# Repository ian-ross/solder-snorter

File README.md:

# Solder Snorter: a PC fan solder fume extractor

*Solder Snorter* is a project I used to learn a little about battery
charging and power conversion. You can read about it
[here](https://www.skybluetrades.net/projects/solder-snorter).

Designed with [KiCad](https://kicad-pcb.org/).

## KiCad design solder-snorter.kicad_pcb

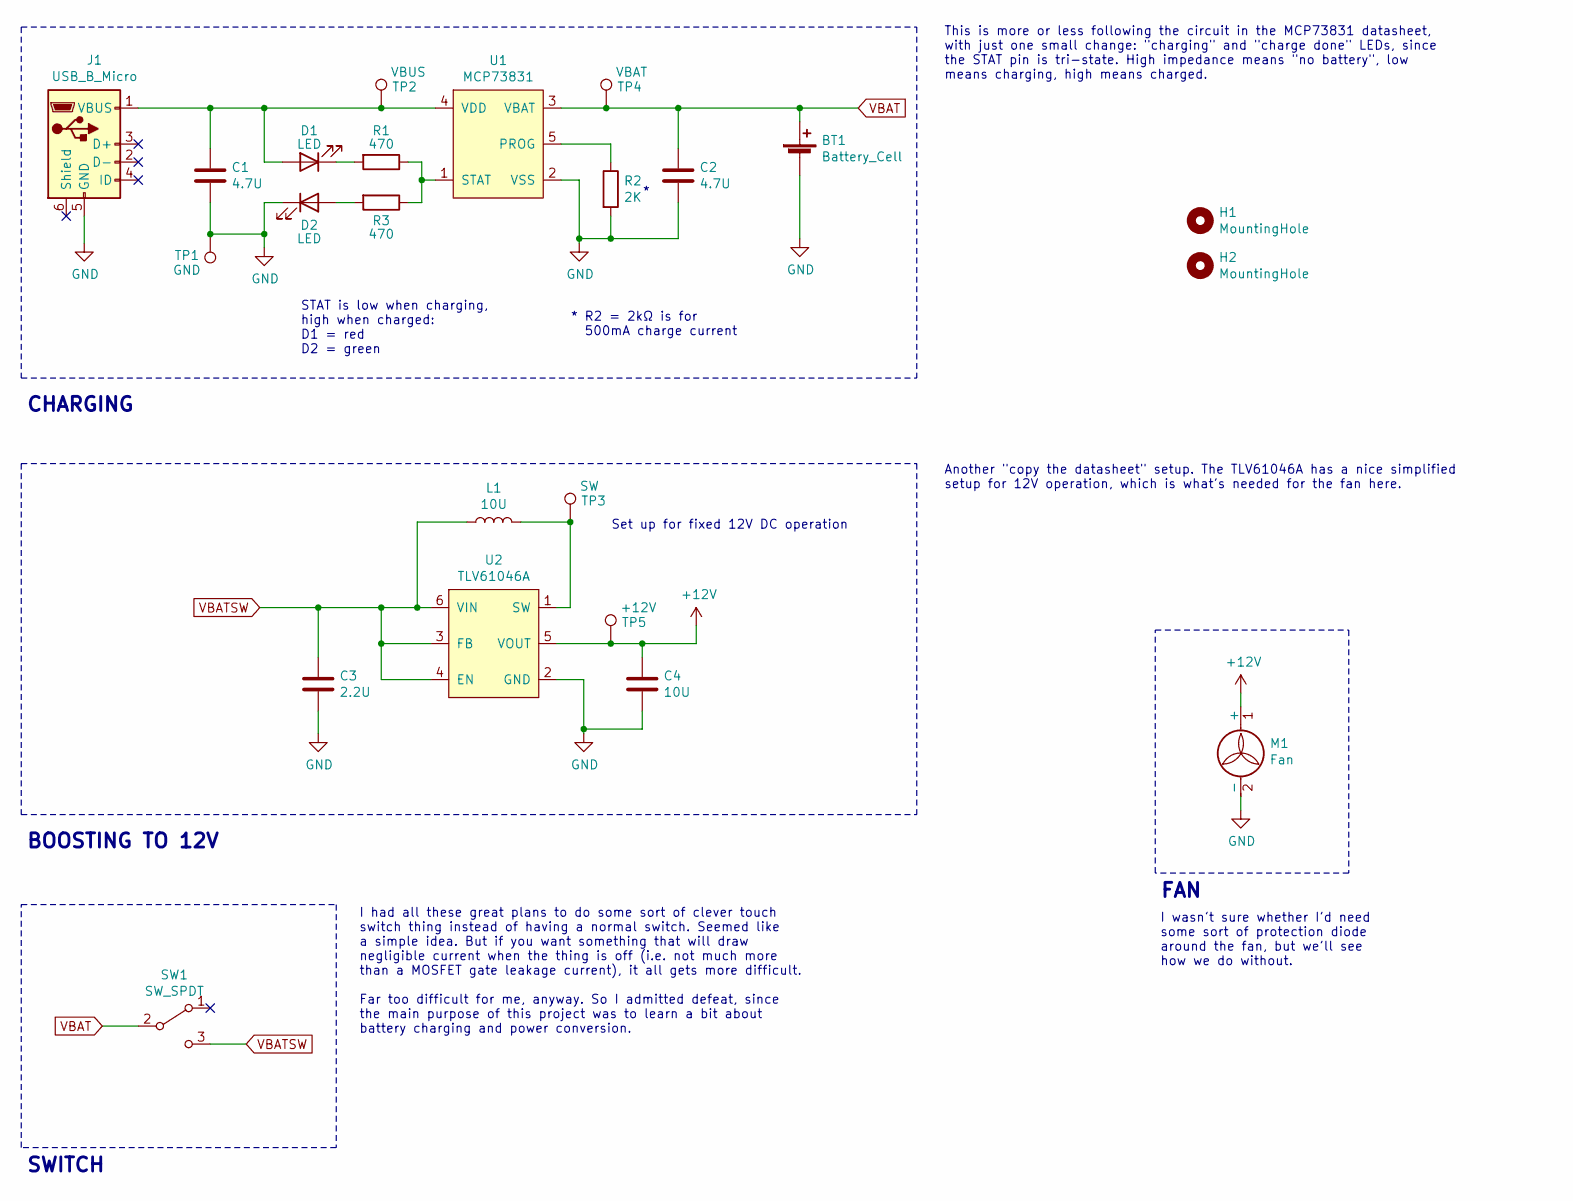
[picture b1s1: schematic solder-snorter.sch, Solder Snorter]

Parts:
BT1: Battery_Cell; BatteryHolder_Keystone_54_1x18650; MPN Keystone 54 (x 2)
C1, C2: 4.7U; C_0805_2012Metric_Pad1.15x1.40mm_HandSolder; MPN 0805X475M250CT
C3: 2.2U; C_0805_2012Metric_Pad1.15x1.40mm_HandSolder; MPN 0805X225M160CT
C4: 10U; C_0805_2012Metric_Pad1.15x1.40mm_HandSolder; MPN C0805C106K4PAC
D1, D2: LED; LED_0805_2012Metric_Pad1.15x1.40mm_HandSolder
H1, H2: MountingHole; MountingHole_4.3mm_M4_DIN965
J1: USB_B_Micro; USB_Micro-B_Amphenol_10118194-0001LF; MPN 10118194-0001LF
L1: 10U; L_Murata_FDSD0420-H-100M; MPN FDSD0420-H-100M=P3
M1: Fan; PinSocket_1x02_P2.54mm_Vertical; MPN CFM-8025V-132-330
R1, R3: 470; R_0805_2012Metric_Pad1.15x1.40mm_HandSolder; MPN CRCW0805470RFKEAC
R2: 2K; R_0805_2012Metric_Pad1.15x1.40mm_HandSolder; MPN CRCW08052K00FKEAC
SW1: SW_SPDT; SW_SPDT_OS102011MA1QN1; MPN OS102011MA1QN1
TP1: GND; TestPoint_Pad_2.0x2.0mm
TP2: VBUS; TestPoint_Pad_2.0x2.0mm
TP3: SW; TestPoint_Pad_2.0x2.0mm
TP4: VBAT; TestPoint_Pad_2.0x2.0mm
TP5: +12V; TestPoint_Pad_2.0x2.0mm
U1: MCP73831; SOT-23-5_HandSoldering; MPN MCP73831T-2ACI/OT
U2: TLV61046A; SOT-23-6_Handsoldering; MPN TLV61046ADBVR

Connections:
+12V: C4.1, M1.1 (+), TP5.1, U2.5 (VOUT)
GND: BT1.2 (-), C1.2, C2.2, C3.2, C4.2, D2.1 (K), J1.5 (GND), M1.2 (-), R2.2, TP1.1, U1.2 (VSS), U2.2 (GND)
unnamed: C1.1, D1.2 (A), J1.1 (VBUS), TP2.1, U1.4 (VDD)
unnamed: D1.1 (K), R1.2
unnamed: D2.2 (A), R3.2
unnamed: L1.2, TP3.1, U2.1 (SW)
unnamed: R1.1, R3.1, U1.1 (STAT)
unnamed: R2.1, U1.5 (PROG)
VBAT: BT1.1 (+), C2.1, SW1.2 (B), TP4.1, U1.3 (VBAT)
VBATSW: C3.1, L1.1, SW1.3 (C), U2.3 (FB), U2.4 (EN), U2.6 (VIN)

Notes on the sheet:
* R2 = 2kΩ is for 500mA charge current
STAT is low when charging, high when charged: D1 = red D2 = green
CHARGING
BOOSTING TO 12V
FAN
Set up for fixed 12V DC operation
SWITCH
I wasn't sure whether I'd need some sort of protection diode around the fan, but we'll see how we do without.
I had all these great plans to do some sort of clever touch switch thing instead of having a normal switch. Seemed like a simple idea. But if you want something that will draw negligible current when the thing is off (i.e. not much more than a MOSFET gate leakage current), it all gets more difficul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
This is more or less following the circuit in the MCP73831 datasheet, with just one small change: "charging" and "charge done" LEDs, since the STAT pin is tri-state. High impedance means "no battery", low means charging, high means charged.
Another "copy the datasheet" setup. The TLV61046A has a nice simplified setup for 12V operation, which is what's needed for the fan here.

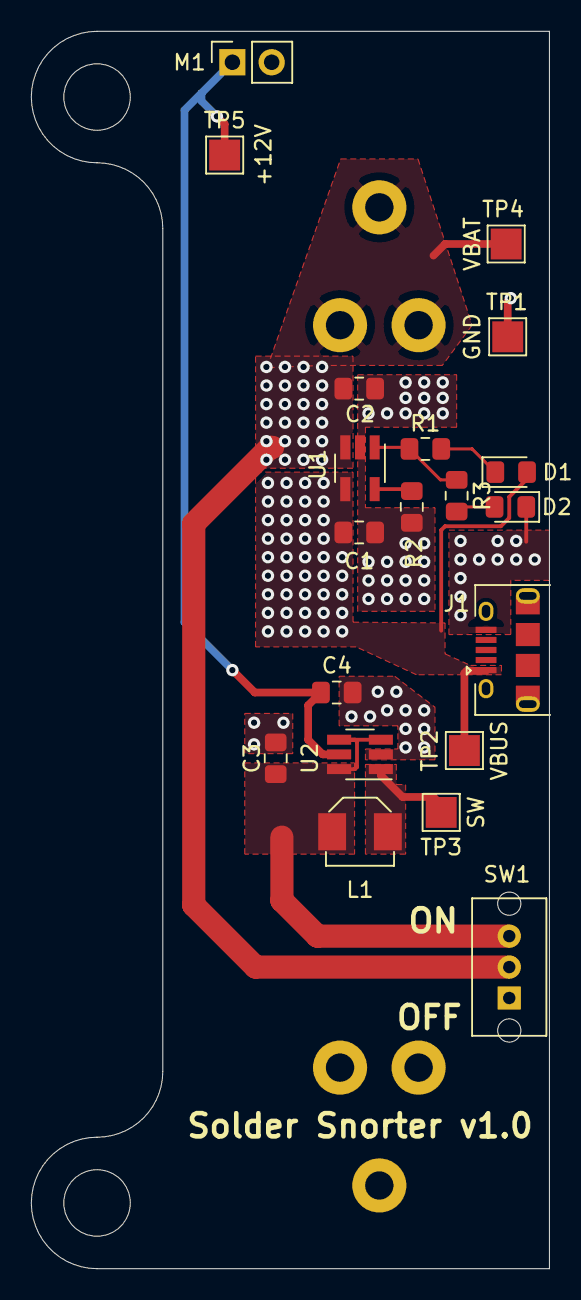
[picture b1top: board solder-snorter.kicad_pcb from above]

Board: 2 copper layers, 33.5 x 80.0 mm, 23 parts (1 on the bottom side), 10 nets.

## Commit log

2020-05-14 Initial schematic
2020-05-17 Footprints done; layout started
2020-05-17 Finished first cut at layout
2020-05-18 Finished v1.0 layout
2020-06-01 v1.0 finished
2020-06-06 Fix LED resistor mistake
